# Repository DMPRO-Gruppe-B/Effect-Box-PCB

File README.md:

# Effect-Box-PCB

View this project on [CADLAB.io](https://cadlab.io/project/2128).

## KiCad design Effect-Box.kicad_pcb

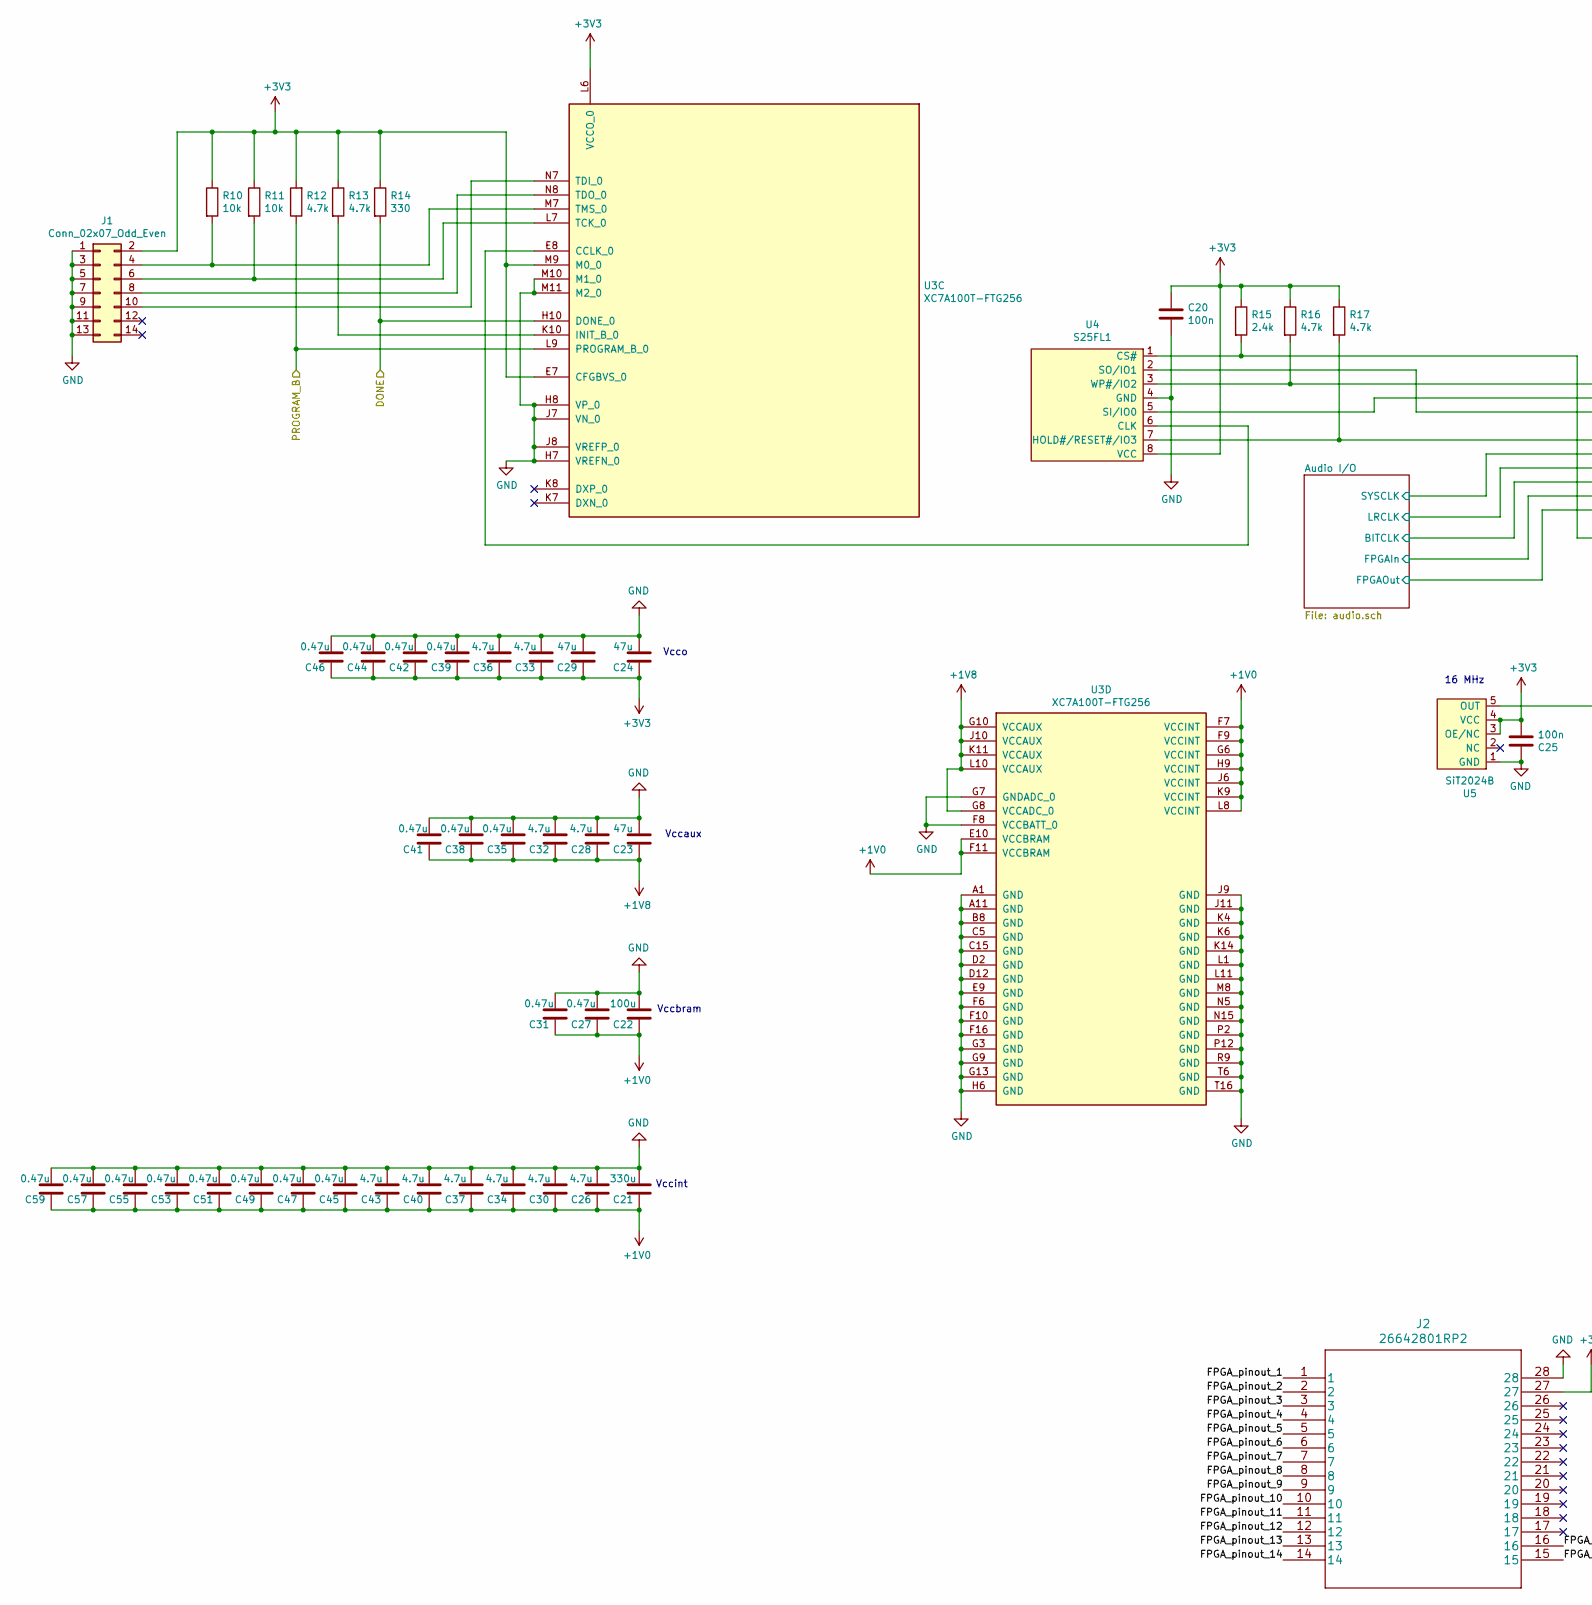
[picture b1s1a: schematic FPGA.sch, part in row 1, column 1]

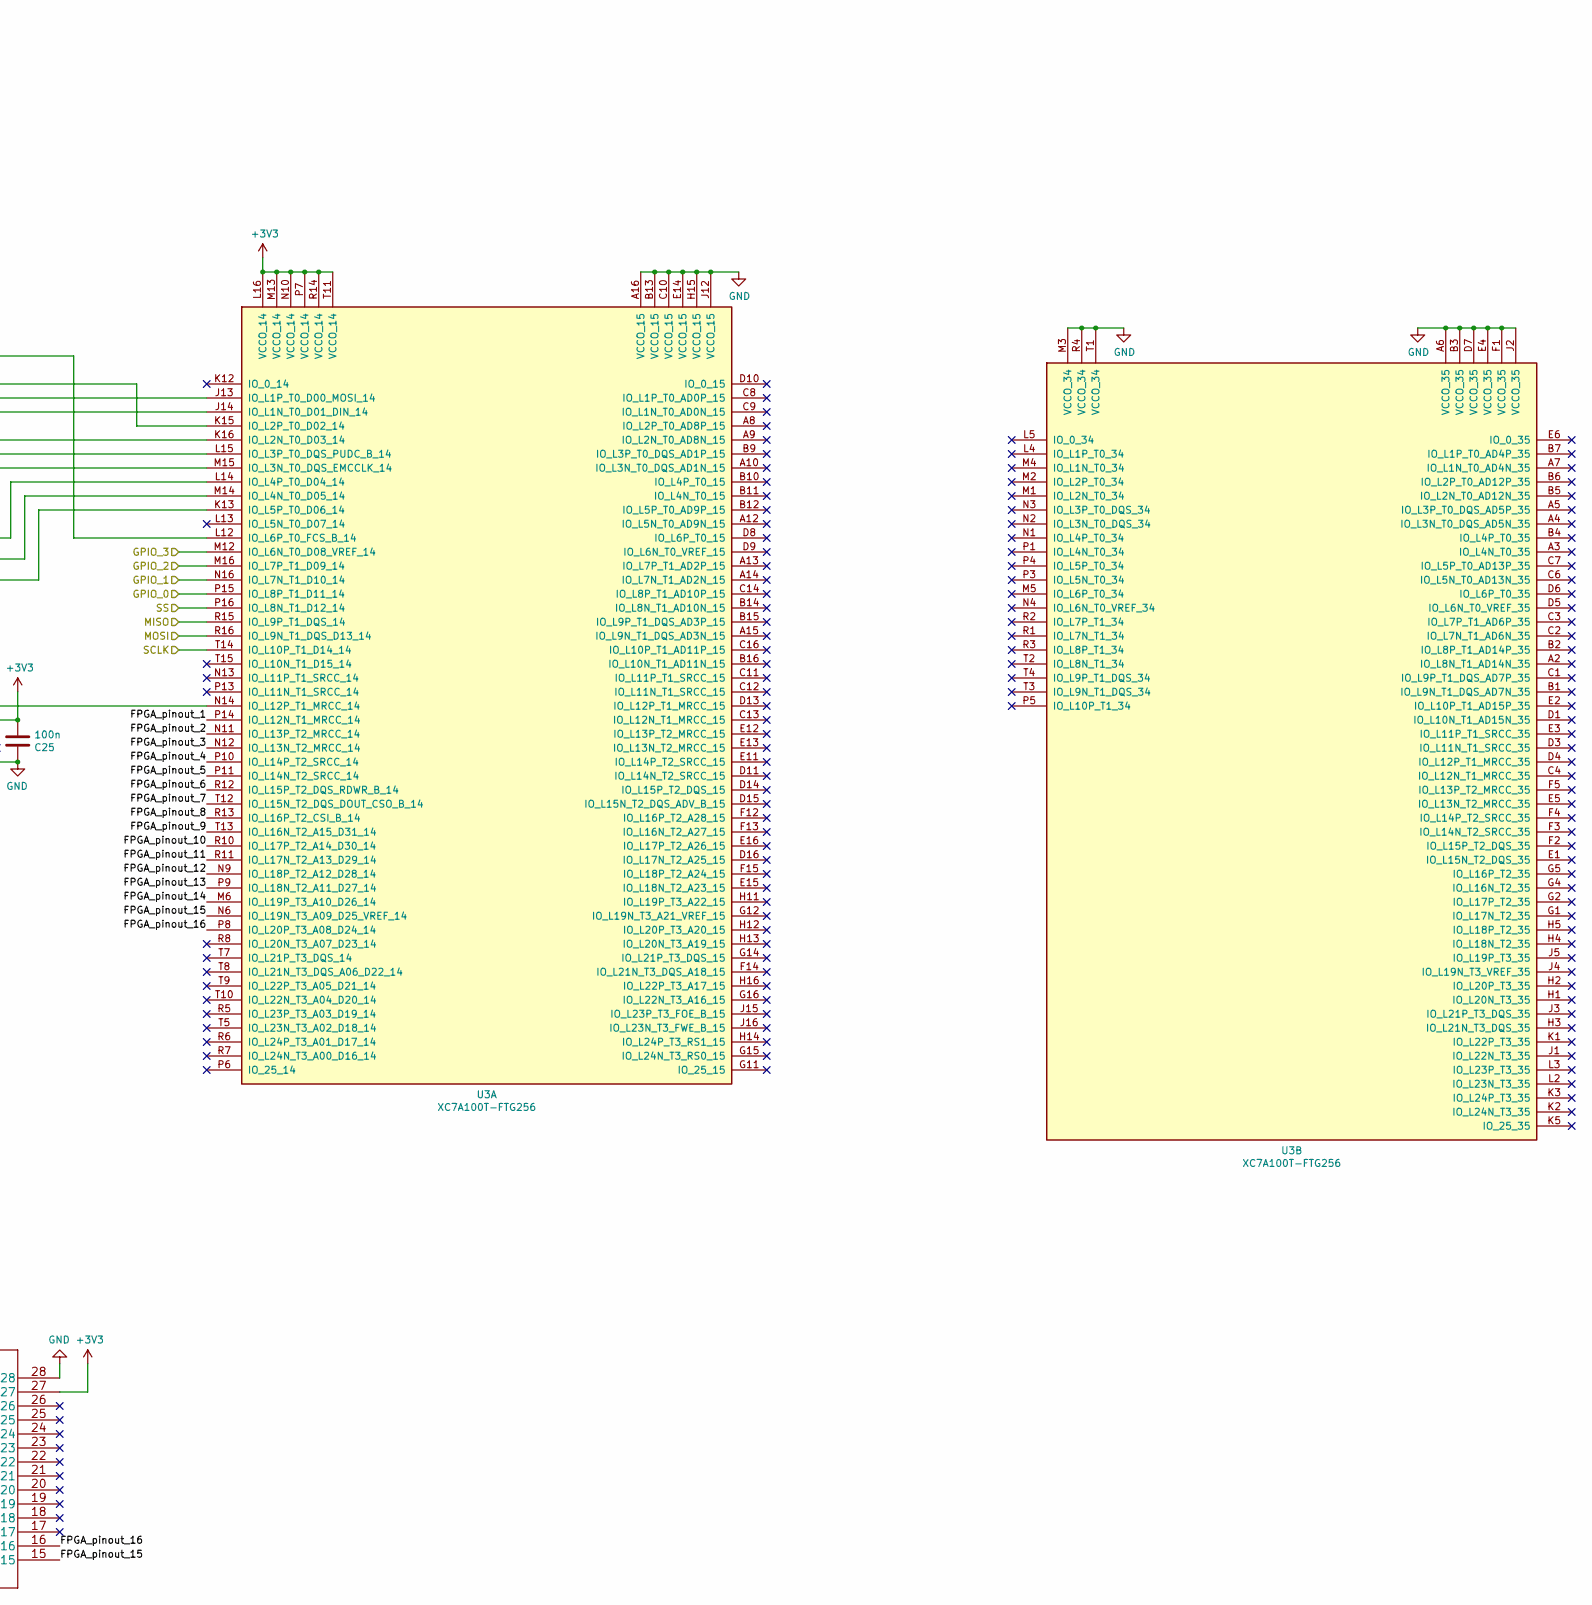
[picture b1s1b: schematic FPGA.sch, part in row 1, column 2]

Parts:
C20, C25: 100n; C_1206_3216Metric_Pad1.42x1.75mm_HandSolder
C21: 330u; C_1206_3216Metric_Pad1.42x1.75mm_HandSolder
C22: 100u; C_1206_3216Metric_Pad1.42x1.75mm_HandSolder
C23, C24, C29: 47u; C_1206_3216Metric_Pad1.42x1.75mm_HandSolder
C26, C28, C30, C32, C33, C34, C36, C37, C40, C43: 4.7u; C_1206_3216Metric_Pad1.42x1.75mm_HandSolder
C27, C31, C35, C38, C39, C41, C42, C44, C45, C46, C47, C49, C51, C53, C55, C57, C59: 0.47u; C_1206_3216Metric_Pad1.42x1.75mm_HandSolder
J1: Conn_02x07_Odd_Even; PinHeader_2x07_P2.00mm_Vertical
J2: 26642801RP2; PinHeader_2x14_P2.54mm_Vertical
R10, R11: 10k; R_1206_3216Metric_Pad1.42x1.75mm_HandSolder
R12, R13, R16, R17: 4.7k; R_1206_3216Metric_Pad1.42x1.75mm_HandSolder
R14: 330; R_1206_3216Metric_Pad1.42x1.75mm_HandSolder
R15: 2.4k; R_1206_3216Metric_Pad1.42x1.75mm_HandSolder
U3: XC7A100T-FTG256; Xilinx_FTG256
U4: S25FL1; SOIC-8_5.275x5.275mm_P1.27mm
U5: SiT2024B; SOT-23-5_HandSoldering

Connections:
+1V0: C21.1, C22.1, C26.1, C27.1, C30.1, C31.1, C34.1, C37.1, C40.1, C43.1, C45.1, C47.1, C49.1, C51.1, C53.1, C55.1, C57.1, C59.1, U3.E10 (VCCBRAM), U3.F7 (VCCINT), U3.F9 (VCCINT), U3.F11 (VCCBRAM), U3.G6 (VCCINT), U3.H9 (VCCINT), U3.J6 (VCCINT), U3.K9 (VCCINT), U3.L8 (VCCINT); also elsewhere on the board
+1V8: C23.1, C28.1, C32.1, C35.1, C38.1, C41.1, U3.G8 (VCCADC_0), U3.G10 (VCCAUX), U3.J10 (VCCAUX), U3.K11 (VCCAUX), U3.L10 (VCCAUX); also elsewhere on the board
/FPGA/Audio I/O/BITCLK: U3.L14 (IO_L4P_T0_D04_14); also elsewhere on the board
/FPGA/Audio I/O/FPGAIn: U3.M14 (IO_L4N_T0_D05_14); also elsewhere on the board
/FPGA/Audio I/O/FPGAOut: U3.K13 (IO_L5P_T0_D06_14); also elsewhere on the board
/FPGA/Audio I/O/LRCLK: U3.M15 (IO_L3N_T0_DQS_EMCCLK_14); also elsewhere on the board
/FPGA/Audio I/O/SYSCLK: U3.L15 (IO_L3P_T0_DQS_PUDC_B_14); also elsewhere on the board
/FPGA/DONE: R14.2, U3.H10 (DONE_0); also elsewhere on the board
/FPGA/FPGA_pinout_1: J2.1, U3.P14 (IO_L12N_T1_MRCC_14)
/FPGA/FPGA_pinout_2: J2.2, U3.N11 (IO_L13P_T2_MRCC_14)
/FPGA/FPGA_pinout_3: J2.3, U3.N12 (IO_L13N_T2_MRCC_14)
/FPGA/FPGA_pinout_4: J2.4, U3.P10 (IO_L14P_T2_SRCC_14)
/FPGA/FPGA_pinout_5: J2.5, U3.P11 (IO_L14N_T2_SRCC_14)
/FPGA/FPGA_pinout_6: J2.6, U3.R12 (IO_L15P_T2_DQS_RDWR_B_14)
/FPGA/FPGA_pinout_7: J2.7, U3.T12 (IO_L15N_T2_DQS_DOUT_CSO_B_14)
/FPGA/FPGA_pinout_8: J2.8, U3.R13 (IO_L16P_T2_CSI_B_14)
/FPGA/FPGA_pinout_9: J2.9, U3.T13 (IO_L16N_T2_A15_D31_14)
/FPGA/FPGA_pinout_10: J2.10, U3.R10 (IO_L17P_T2_A14_D30_14)
/FPGA/FPGA_pinout_11: J2.11, U3.R11 (IO_L17N_T2_A13_D29_14)
/FPGA/FPGA_pinout_12: J2.12, U3.N9 (IO_L18P_T2_A12_D28_14)
/FPGA/FPGA_pinout_13: J2.13, U3.P9 (IO_L18N_T2_A11_D27_14)
/FPGA/FPGA_pinout_14: J2.14, U3.M6 (IO_L19P_T3_A10_D26_14)
/FPGA/FPGA_pinout_15: J2.15, U3.N6 (IO_L19N_T3_A09_D25_VREF_14)
/FPGA/FPGA_pinout_16: J2.16, U3.P8 (IO_L20P_T3_A08_D24_14)
/FPGA/GPIO_0: U3.P15 (IO_L8P_T1_D11_14); also elsewhere on the board
/FPGA/GPIO_1: U3.N16 (IO_L7N_T1_D10_14); also elsewhere on the board
/FPGA/GPIO_2: U3.M16 (IO_L7P_T1_D09_14); also elsewhere on the board
/FPGA/GPIO_3: U3.M12 (IO_L6N_T0_D08_VREF_14); also elsewhere on the board
/FPGA/MISO: U3.R15 (IO_L9P_T1_DQS_14); also elsewhere on the board
/FPGA/MOSI: U3.R16 (IO_L9N_T1_DQS_D13_14); also elsewhere on the board
/FPGA/PROGRAM_B: R12.1, U3.L9 (PROGRAM_B_0); also elsewhere on the board
/FPGA/SCLK: U3.T14 (IO_L10P_T1_D14_14); also elsewhere on the board
/FPGA/SS: U3.P16 (IO_L8N_T1_D12_14); also elsewhere on the board
GND: C20.2, C21.2, C22.2, C23.2, C24.2, C25.1, C26.2, C27.2, C28.2, C29.2, C30.2, C31.2, C32.2, C33.2, C34.2, C35.2, C36.2, C37.2, C38.2, C39.2, C40.2, C41.2, C42.2, C43.2, C44.2, C45.2, C46.2, C47.2, C49.2, C51.2, C53.2, C55.2, C57.2, C59.2, J1.1, J1.3, J1.5, J1.7, J1.9, J1.11, J1.13, J2.28, U3.A1 (GND), U3.A6 (VCCO_35), U3.A11 (GND), U3.A16 (VCCO_15), U3.B3 (VCCO_35), U3.B8 (GND), U3.B13 (VCCO_15), U3.C5 (GND), U3.C10 (VCCO_15), U3.C15 (GND), U3.D2 (GND), U3.D7 (VCCO_35), U3.D12 (GND), U3.E4 (VCCO_35), U3.E9 (GND), U3.E14 (VCCO_15), U3.F1 (VCCO_35), U3.F6 (GND), U3.F8 (VCCBATT_0), U3.F10 (GND), U3.F16 (GND), U3.G3 (GND), U3.G7 (GNDADC_0), U3.G9 (GND), U3.G13 (GND), U3.H6 (GND), U3.H7 (VREFN_0), U3.H8 (VP_0), U3.H15 (VCCO_15), U3.J2 (VCCO_35), U3.J7 (VN_0), U3.J8 (VREFP_0), U3.J9 (GND), U3.J11 (GND), U3.J12 (VCCO_15), U3.K4 (GND), U3.K6 (GND), U3.K14 (GND), U3.L1 (GND), U3.L11 (GND), U3.M3 (VCCO_34), U3.M8 (GND), U3.M10 (M1_0), U3.M11 (M2_0), U3.N5 (GND), U3.N15 (GND), U3.P2 (GND), U3.P12 (GND), U3.R4 (VCCO_34), U3.R9 (GND), U3.T1 (VCCO_34), U3.T6 (GND), U3.T16 (GND), U4.4 (GND), U5.1 (GND); also elsewhere on the board
unnamed: J1.4, R10.2, U3.M7 (TMS_0)
unnamed: J1.6, R11.2, U3.L7 (TCK_0)
unnamed: J1.8, U3.N8 (TDO_0)
unnamed: J1.10, U3.N7 (TDI_0)
unnamed: R13.2, U3.K10 (INIT_B_0)
unnamed: R15.2, U3.L12 (IO_L6P_T0_FCS_B_14), U4.1 (CS#)
unnamed: R16.2, U3.K15 (IO_L2P_T0_D02_14), U4.3 (WP#/IO2)
unnamed: R17.2, U3.K16 (IO_L2N_T0_D03_14), U4.7 (HOLD#/RESET#/IO3)
unnamed: U3.E8 (CCLK_0), U4.6 (CLK)
unnamed: U3.J13 (IO_L1P_T0_D00_MOSI_14), U4.5 (SI/IO0)
unnamed: U3.J14 (IO_L1N_T0_D01_DIN_14), U4.2 (SO/IO1)
unnamed: U3.N14 (IO_L12P_T1_MRCC_14), U5.5 (OUT)

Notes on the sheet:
16 MHz
Vccbram
Vccaux
Vcco
Vccint

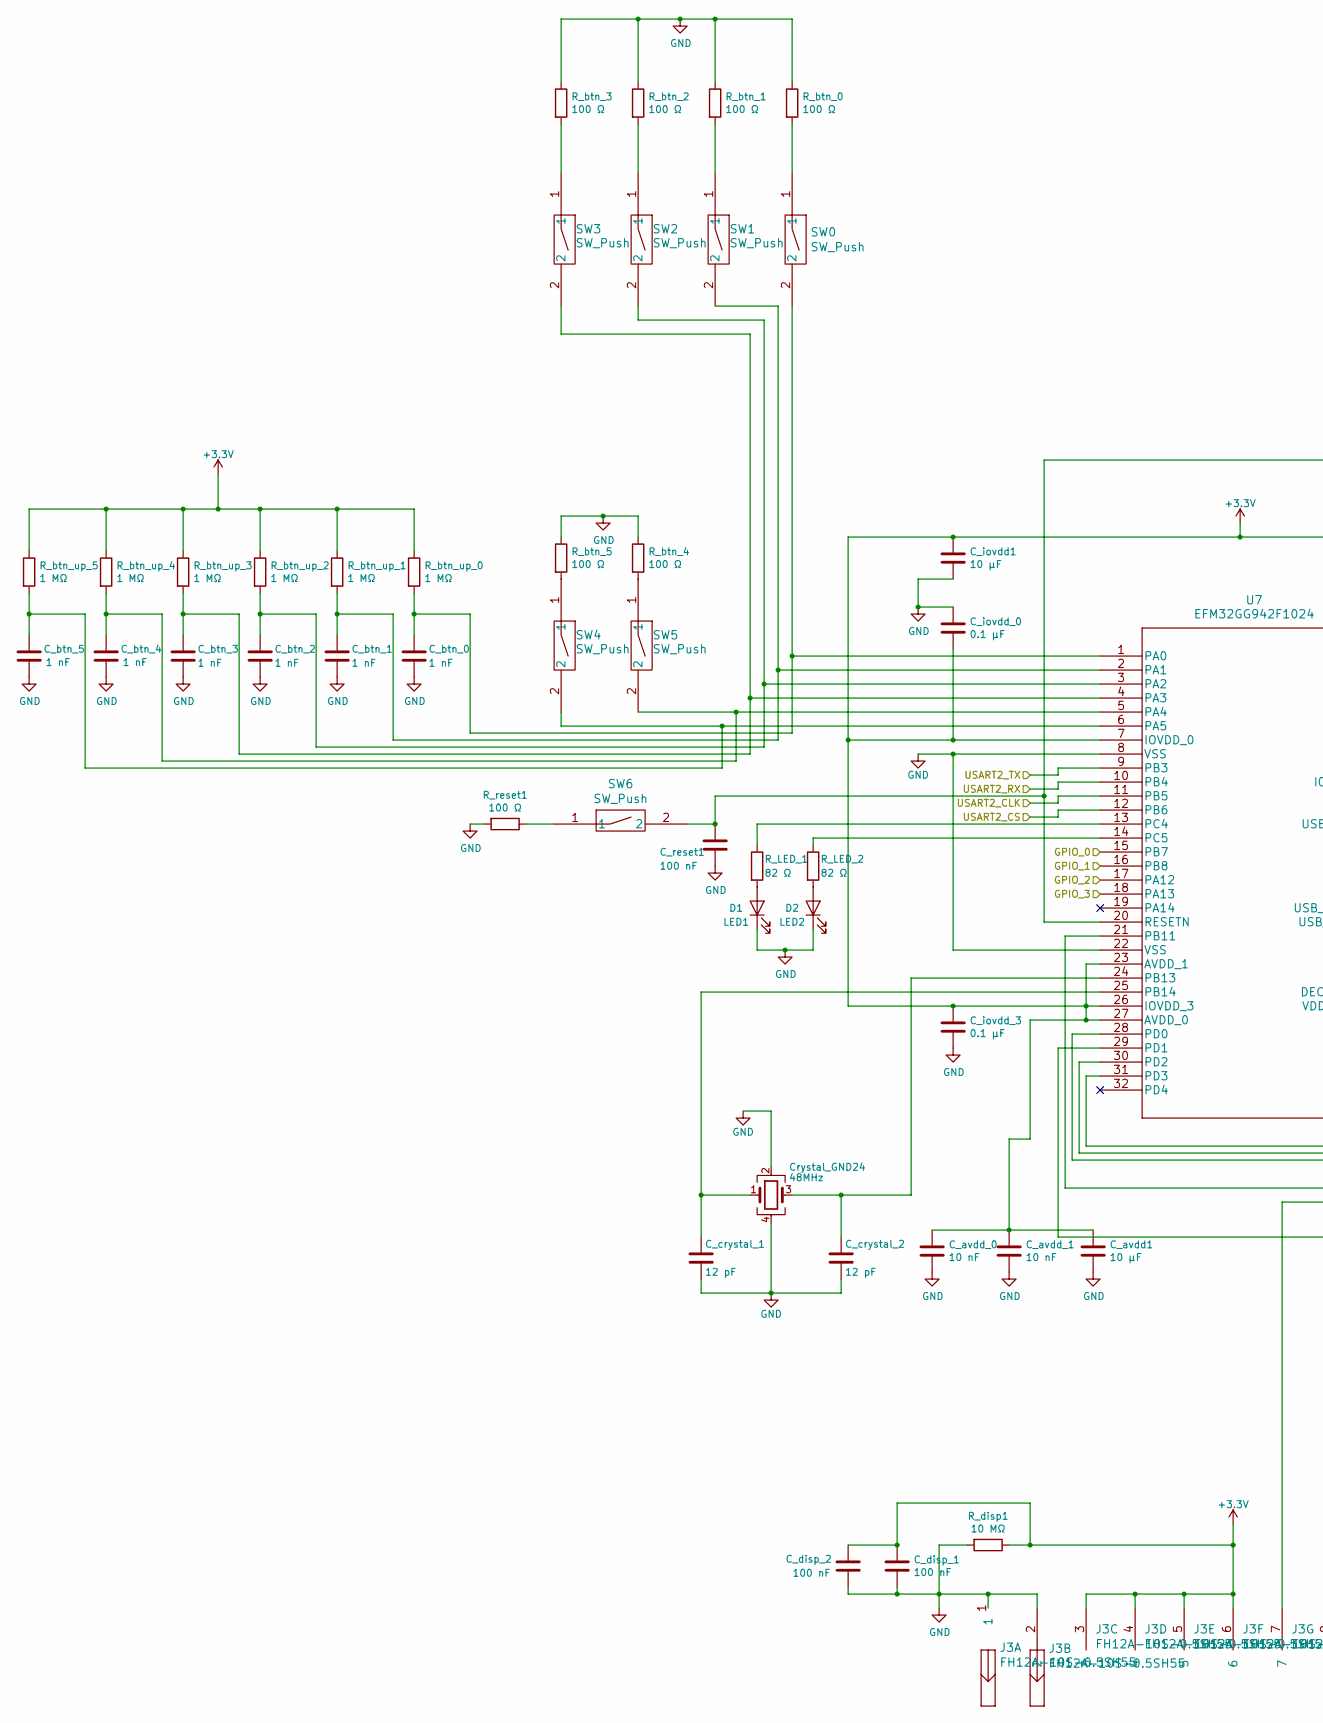
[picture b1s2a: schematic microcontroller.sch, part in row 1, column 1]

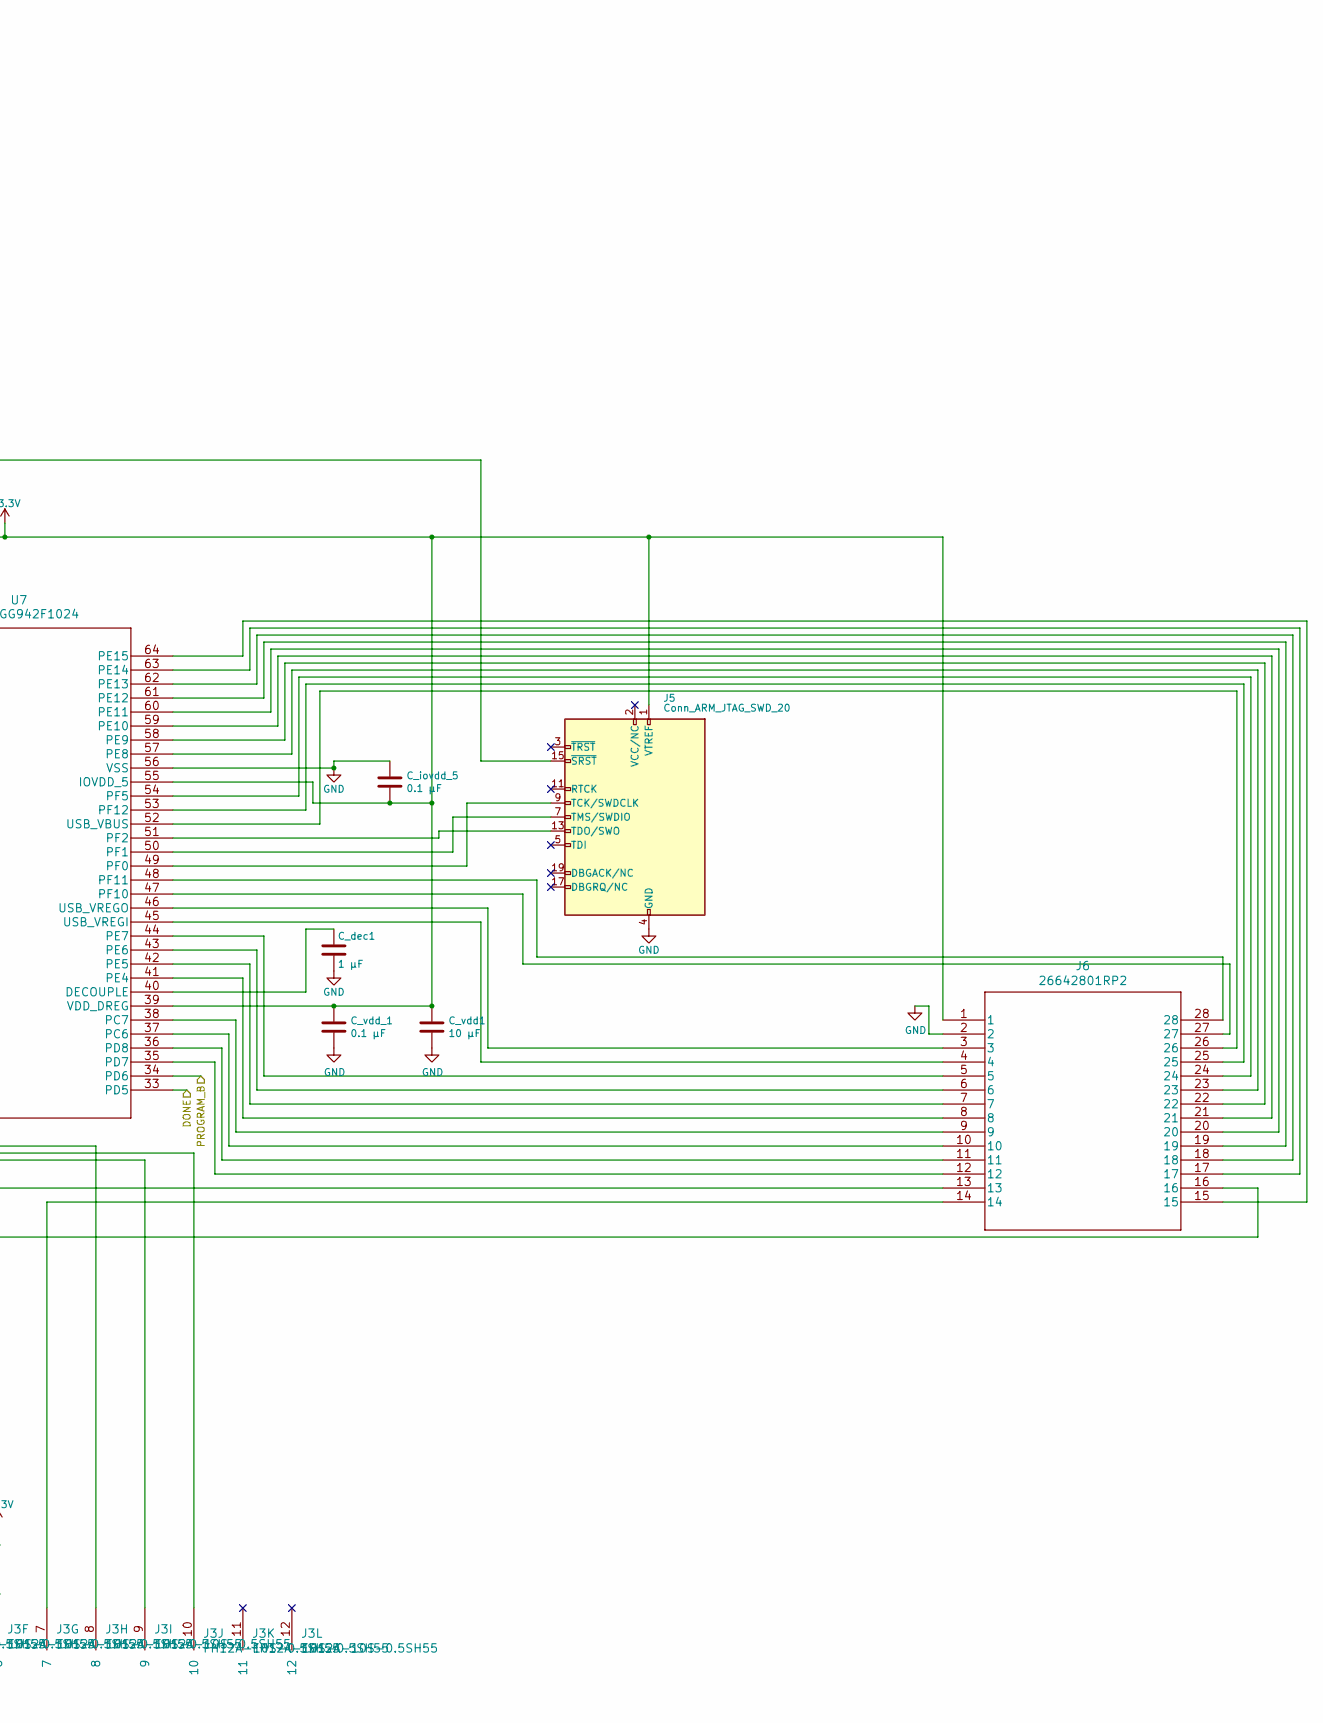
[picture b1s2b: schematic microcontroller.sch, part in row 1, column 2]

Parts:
C_avdd1: 10 µF; C_1206_3216Metric_Pad1.42x1.75mm_HandSolder
C_avdd_0, C_avdd_1: 10 nF; C_1206_3216Metric_Pad1.42x1.75mm_HandSolder
C_btn_0, C_btn_1, C_btn_2, C_btn_3, C_btn_4, C_btn_5: 1 nF; C_1206_3216Metric_Pad1.42x1.75mm_HandSolder
C_crystal_1, C_crystal_2: 12 pF; C_1206_3216Metric_Pad1.42x1.75mm_HandSolder
C_dec1: 1 µF; C_1206_3216Metric_Pad1.42x1.75mm_HandSolder
C_disp_1, C_disp_2: 100 nF; C_1206_3216Metric_Pad1.42x1.75mm_HandSolder
C_iovdd1: 10 µF; C_1206_3216Metric_Pad1.42x1.75mm_HandSolder
C_iovdd_0, C_iovdd_3, C_iovdd_5: 0.1 µF; C_1206_3216Metric_Pad1.42x1.75mm_HandSolder
C_reset1: 100 nF; C_1206_3216Metric_Pad1.42x1.75mm_HandSolder
C_vdd1: 10 µF; C_1206_3216Metric_Pad1.42x1.75mm_HandSolder
C_vdd_1: 0.1 µF; C_1206_3216Metric_Pad1.42x1.75mm_HandSolder
Crystal_GND24: 48MHz; Crystal_SMD_Abracon_ABM8G-4Pin_3.2x2.5mm
D1: LED1; LED_0805_2012Metric_Pad1.15x1.40mm_HandSolder
D2: LED2; LED_0805_2012Metric_Pad1.15x1.40mm_HandSolder
J3: FH12A-10S-0.5SH55
J5: Conn_ARM_JTAG_SWD_20; PinHeader_2x10_P2.54mm_Vertical
J6: 26642801RP2; PinHeader_2x14_P2.54mm_Vertical
R_LED_1, R_LED_2: 82 Ω; R_1206_3216Metric_Pad1.42x1.75mm_HandSolder
R_btn_0, R_btn_1, R_btn_2, R_btn_3, R_btn_4, R_btn_5: 100 Ω; R_1206_3216Metric_Pad1.42x1.75mm_HandSolder
R_btn_up_0, R_btn_up_1, R_btn_up_2, R_btn_up_3, R_btn_up_4, R_btn_up_5: 1 MΩ; R_1206_3216Metric_Pad1.42x1.75mm_HandSolder
R_disp1: 10 MΩ; R_1206_3216Metric_Pad1.42x1.75mm_HandSolder
R_reset1: 100 Ω; R_1206_3216Metric_Pad1.42x1.75mm_HandSolder
SW0, SW1, SW2, SW3, SW4, SW5, SW6: SW_Push; FSMSMTR
U7: EFM32GG942F1024

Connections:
/FPGA/DONE: U7.33 (PD5); also elsewhere on the board
/FPGA/GPIO_0: U7.15 (PB7); also elsewhere on the board
/FPGA/GPIO_1: U7.16 (PB8); also elsewhere on the board
/FPGA/GPIO_2: U7.17 (PA12); also elsewhere on the board
/FPGA/GPIO_3: U7.18 (PA13); also elsewhere on the board
/FPGA/MISO: U7.10 (PB4); also elsewhere on the board
/FPGA/MOSI: U7.9 (PB3); also elsewhere on the board
/FPGA/PROGRAM_B: U7.34 (PD6); also elsewhere on the board
/FPGA/SCLK: U7.11 (PB5); also elsewhere on the board
/FPGA/SS: U7.12 (PB6); also elsewhere on the board
GND: C_avdd1.2, C_avdd_0.2, C_avdd_1.2, C_btn_0.2, C_btn_1.2, C_btn_2.2, C_btn_3.2, C_btn_4.2, C_btn_5.2, C_crystal_1.2, C_crystal_2.2, C_dec1.2, C_disp_1.2, C_disp_2.2, C_iovdd1.2, C_iovdd_0.1, C_iovdd_3.2, C_iovdd_5.1, C_reset1.2, C_vdd1.2, C_vdd_1.2, Crystal_GND24.2, Crystal_GND24.4, D1.1 (K), D2.1 (K), J3.1, J3.2, J5.4 (GND), J5.6 (GND), J5.8 (GND), J5.10 (GND), J5.12 (GND), J5.14 (GND), J5.16 (GND), J5.18 (GND), J5.20 (GND), J6.2, R_btn_0.1, R_btn_1.1, R_btn_2.1, R_btn_3.1, R_btn_4.1, R_btn_5.1, R_disp1.2, R_reset1.2, U7.8 (VSS), U7.22 (VSS), U7.56 (VSS); also elsewhere on the board
unnamed: C_btn_0.1, R_btn_up_0.2, SW0.2, U7.1 (PA0)
unnamed: C_btn_1.1, R_btn_up_1.2, SW1.2, U7.2 (PA1)
unnamed: C_btn_2.1, R_btn_up_2.2, SW2.2, U7.3 (PA2)
unnamed: C_btn_3.1, R_btn_up_3.2, SW3.2, U7.4 (PA3)
unnamed: C_btn_4.1, R_btn_up_4.2, SW5.2, U7.5 (PA4)
unnamed: C_btn_5.1, R_btn_up_5.2, SW4.2, U7.6 (PA5)
unnamed: C_crystal_1.1, Crystal_GND24.1, U7.25 (PB14)
unnamed: C_crystal_2.1, Crystal_GND24.3, U7.24 (PB13)
unnamed: C_dec1.1, U7.40 (DECOUPLE)
unnamed: C_reset1.1, J5.15 (~SRST~), SW6.2, U7.20 (RESETN)
unnamed: D1.2 (A), R_LED_1.2
unnamed: D2.2 (A), R_LED_2.2
unnamed: J3.7, J6.14
unnamed: J3.8, U7.31 (PD3)
unnamed: J3.9, U7.28 (PD0)
unnamed: J3.10, U7.30 (PD2)
unnamed: J5.7 (TMS/SWDIO), U7.50 (PF1)
unnamed: J5.9 (TCK/SWDCLK), U7.49 (PF0)
unnamed: J5.13 (TDO/SWO), U7.51 (PF2)
unnamed: J6.3, U7.46 (USB_VREGO)
unnamed: J6.4, U7.45 (USB_VREGI)
unnamed: J6.5, U7.44 (PE7)
unnamed: J6.6, U7.43 (PE6)
unnamed: J6.7, U7.42 (PE5)
unnamed: J6.8, U7.41 (PE4)
unnamed: J6.9, U7.38 (PC7)
unnamed: J6.10, U7.37 (PC6)
unnamed: J6.11, U7.36 (PD8)
unnamed: J6.12, U7.35 (PD7)
unnamed: J6.13, U7.21 (PB11)
unnamed: J6.15, U7.64 (PE15)
unnamed: J6.16, U7.29 (PD1)
unnamed: J6.17, U7.63 (PE14)
unnamed: J6.18, U7.62 (PE13)
unnamed: J6.19, U7.61 (PE12)
unnamed: J6.20, U7.60 (PE11)
unnamed: J6.21, U7.59 (PE10)
unnamed: J6.22, U7.58 (PE9)
unnamed: J6.23, U7.57 (PE8)
unnamed: J6.24, U7.54 (PF5)
unnamed: J6.25, U7.53 (PF12)
unnamed: J6.26, U7.52 (USB_VBUS)
unnamed: J6.27, U7.47 (PF10)
unnamed: J6.28, U7.48 (PF11)
unnamed: R_LED_1.1, U7.13 (PC4)
unnamed: R_LED_2.1, U7.14 (PC5)
unnamed: R_btn_0.2, SW0.1
unnamed: R_btn_1.2, SW1.1
unnamed: R_btn_2.2, SW2.1
unnamed: R_btn_3.2, SW3.1
unnamed: R_btn_4.2, SW5.1
unnamed: R_btn_5.2, SW4.1
unnamed: R_reset1.1, SW6.1

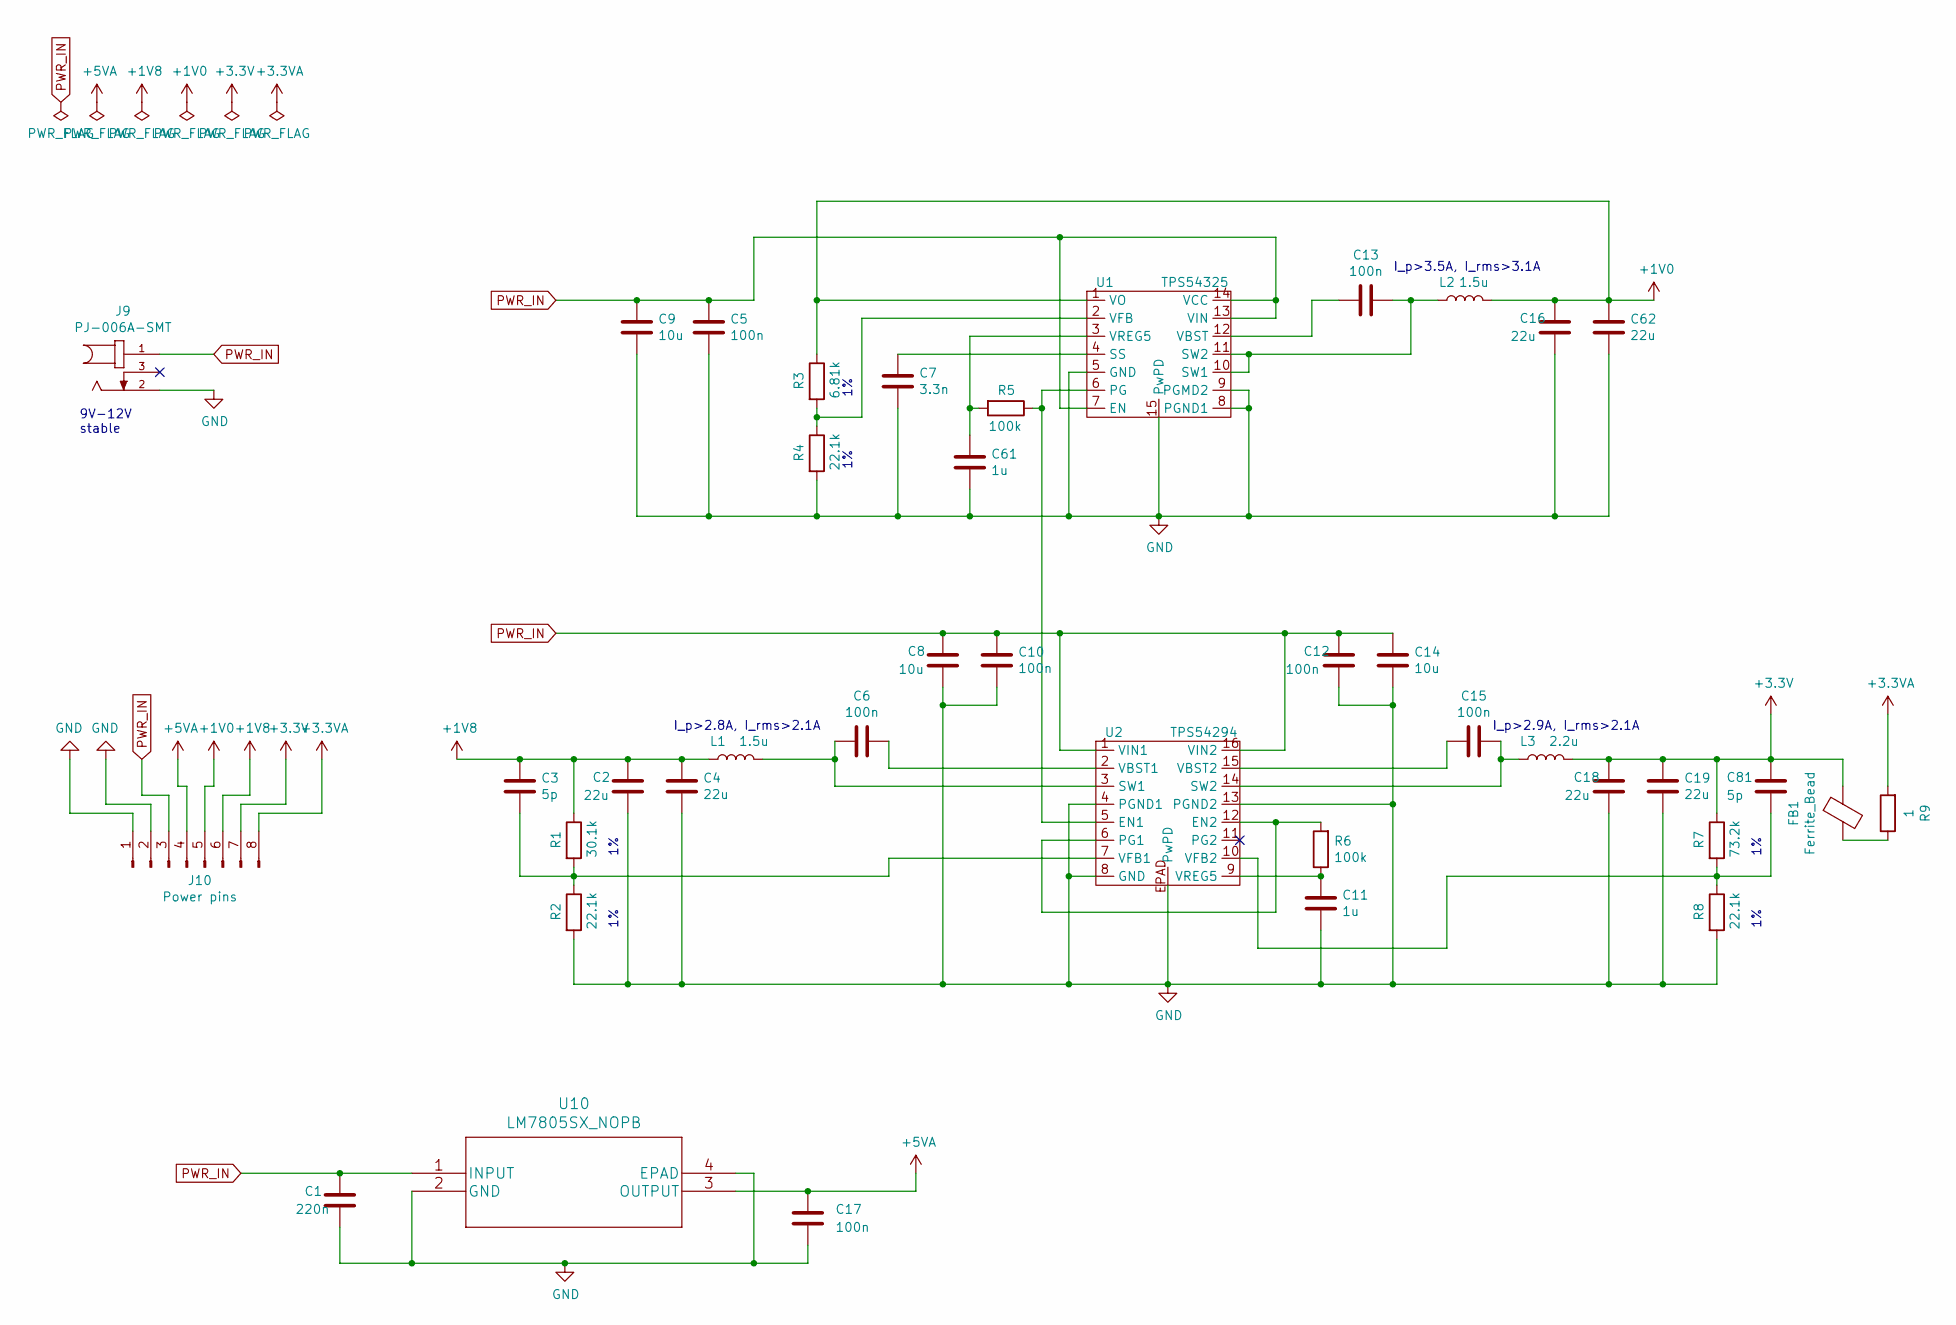
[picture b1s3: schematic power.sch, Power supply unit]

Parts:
C1: 220n; C_1206_3216Metric_Pad1.42x1.75mm_HandSolder
C2, C4, C16, C18, C19, C62: 22u; C_1206_3216Metric_Pad1.42x1.75mm_HandSolder
C3, C81: 5p; C_1206_3216Metric_Pad1.42x1.75mm_HandSolder
C5, C6, C10, C12, C13, C15, C17: 100n; C_1206_3216Metric_Pad1.42x1.75mm_HandSolder
C7: 3.3n; C_1206_3216Metric_Pad1.42x1.75mm_HandSolder
C8, C9, C14: 10u; C_1206_3216Metric_Pad1.42x1.75mm_HandSolder
C11, C61: 1u; C_1206_3216Metric_Pad1.42x1.75mm_HandSolder
FB1: Ferrite_Bead; BLM21AG102SN1D
J9: PJ-006A-SMT; CUI_PJ-006A-SMT
J10: Power pins; PinHeader_1x08_P2.54mm_Vertical
L1, L2: 1.5u; IND_VLS5045EX-4R7M
L3: 2.2u; IND_VLS5045EX-4R7M
R1: 30.1k; R_1206_3216Metric_Pad1.42x1.75mm_HandSolder
R2, R4, R8: 22.1k; R_1206_3216Metric_Pad1.42x1.75mm_HandSolder
R3: 6.81k; R_1206_3216Metric_Pad1.42x1.75mm_HandSolder
R5, R6: 100k; R_1206_3216Metric_Pad1.42x1.75mm_HandSolder
R7: 73.2k; R_1206_3216Metric_Pad1.42x1.75mm_HandSolder
R9: 1; R_1206_3216Metric_Pad1.42x1.75mm_HandSolder
U1: TPS54325; TPS54325PWPR
U2: TPS54294; TPS54294PWPR
U10: LM7805SX_NOPB; LM7805SX&slash_NOPB

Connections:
+1V0: C16.1, C62.1, J10.5, L2.2, R3.1, U1.1 (VO); also elsewhere on the board
+1V8: C2.1, C3.1, C4.1, J10.6, L1.1, R1.1; also elsewhere on the board
+3.3VA: J10.8, R9.2; also elsewhere on the board
+5VA: C17.1, J10.4, U10.3 (OUTPUT); also elsewhere on the board
GND: C1.2, C2.2, C4.2, C5.2, C7.2, C8.2, C9.2, C10.2, C11.2, C12.2, C14.2, C16.2, C17.2, C18.2, C19.2, C61.2, C62.2, J9.2, J10.1, J10.2, R2.2, R4.2, R8.2, U1.5 (GND), U1.8 (PGND1), U1.9 (PGMD2), U1.15 (PwPD), U2.4 (PGND1), U2.8 (GND), U2.13 (PGND2), U2.EPAD (PwPD), U10.2 (GND), U10.4 (EPAD); also elsewhere on the board
unnamed: C3.2, R1.2, R2.1, U2.7 (VFB1)
unnamed: C6.1, U2.2 (VBST1)
unnamed: C6.2, L1.2, U2.3 (SW1)
unnamed: C7.1, U1.4 (SS)
unnamed: C11.1, R6.1, U2.9 (VREG5)
unnamed: C13.1, L2.1, U1.10 (SW1), U1.11 (SW2)
unnamed: C13.2, U1.12 (VBST)
unnamed: C15.1, L3.1, U2.14 (SW2)
unnamed: C15.2, U2.15 (VBST2)
unnamed: C61.1, R5.2, U1.3 (VREG5)
unnamed: C81.2, R7.2, R8.1, U2.10 (VFB2)
unnamed: FB1.2, R9.1
unnamed: R3.2, R4.1, U1.2 (VFB)
unnamed: R5.1, U1.6 (PG), U2.5 (EN1)
unnamed: R6.2, U2.6 (PG1), U2.12 (EN2)
PWR_IN: C1.1, C5.1, C8.1, C9.1, C10.1, C12.1, C14.1, J9.1, J10.3, U1.7 (EN), U1.13 (VIN), U1.14 (VCC), U2.1 (VIN1), U2.16 (VIN2), U10.1 (INPUT)

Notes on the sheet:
I_p>2.9A, I_rms>2.1A
I_p>2.8A, I_rms>2.1A
I_p>3.5A, I_rms>3.1A
9V-12V stable

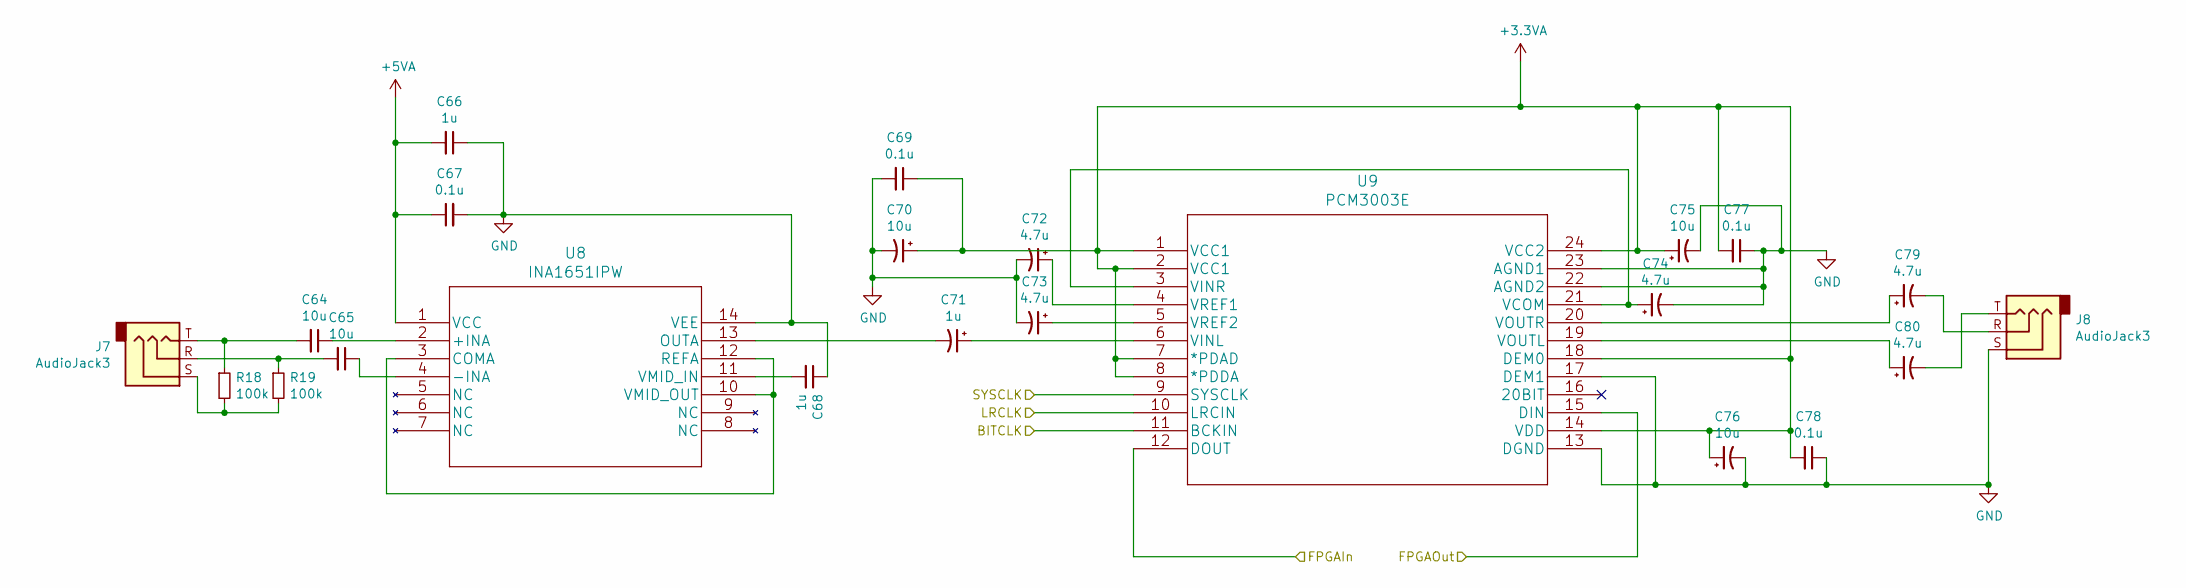
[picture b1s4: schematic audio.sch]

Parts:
C64, C65, C70, C75, C76: 10u; C_1206_3216Metric_Pad1.42x1.75mm_HandSolder
C66, C68, C71: 1u; C_1206_3216Metric_Pad1.42x1.75mm_HandSolder
C67, C69, C77, C78: 0.1u; C_1206_3216Metric_Pad1.42x1.75mm_HandSolder
C72, C73, C74, C79, C80: 4.7u; C_1206_3216Metric_Pad1.42x1.75mm_HandSolder
J7, J8: AudioJack3; Jack_3.5mm_CUI_SJ-3523-SMT_Horizontal
R18, R19: 100k; R_1206_3216Metric_Pad1.42x1.75mm_HandSolder
U8: INA1651IPW; TSSOP-14_4.4x5mm_P0.65mm
U9: PCM3003E; SSOP-24_5.3x8.2mm_P0.65mm

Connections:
+3.3VA: C69.1, C70.1, C75.1, C76.1, C77.2, C78.2, U9.1 (VCC1), U9.2 (VCC1), U9.7 (*PDAD), U9.8 (*PDDA), U9.14 (VDD), U9.18 (DEM0), U9.24 (VCC2); also elsewhere on the board
+5VA: C66.2, C67.1, U8.1 (VCC); also elsewhere on the board
/FPGA/Audio I/O/BITCLK: U9.11 (BCKIN); also elsewhere on the board
/FPGA/Audio I/O/FPGAIn: U9.12 (DOUT); also elsewhere on the board
/FPGA/Audio I/O/FPGAOut: U9.15 (DIN); also elsewhere on the board
/FPGA/Audio I/O/LRCLK: U9.10 (LRCIN); also elsewhere on the board
/FPGA/Audio I/O/SYSCLK: U9.9 (SYSCLK); also elsewhere on the board
GND: C66.1, C67.2, C68.1, C69.2, C70.2, C72.2, C73.2, C74.2, C75.2, C76.2, C77.1, C78.1, J8.S, U8.14 (VEE), U9.13 (DGND), U9.17 (DEM1), U9.22 (AGND2), U9.23 (AGND1); also elsewhere on the board
unnamed: C64.1, U8.2 (+INA)
unnamed: C64.2, J7.T, R18.1
unnamed: C65.1, U8.4 (-INA)
unnamed: C65.2, J7.R, R19.1
unnamed: C68.2, U8.11 (VMID_IN)
unnamed: C71.1, U9.6 (VINL)
unnamed: C71.2, U8.13 (OUTA)
unnamed: C72.1, U9.4 (VREF1)
unnamed: C73.1, U9.5 (VREF2)
unnamed: C74.1, U9.3 (VINR), U9.21 (VCOM)
unnamed: C79.1, U9.20 (VOUTR)
unnamed: C79.2, J8.R
unnamed: C80.1, U9.19 (VOUTL)
unnamed: C80.2, J8.T
unnamed: J7.S, R18.2, R19.2
unnamed: U8.3 (COMA), U8.10 (VMID_OUT), U8.12 (REFA)

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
